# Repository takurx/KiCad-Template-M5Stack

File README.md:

# KiCad-Template-M5Stack
a PCB template of modules of M5Stack with footprints for KiCad.

## for KiCad 9
- Changed file name and folder structure to KiCad 9 from KiCad 6.
    - file name: bf-021.kicad_pcb  <-  bf-021_pcb.kicad
    - folder structure 1: ./bf-021.kicad_pcb  <-  bf-021/bf-021_pcb.kicad
    - folder structure 2: ./meta/  <-  bf-021/meta/

- Example of KiCad 9
```
C:\Users\ChinoKafu\Documents\KiCad\9.0\template\KiCad-Template-M5Stack>tree /f /a .
フォルダー パスの一覧:  ボリューム OS
ボリューム シリアル番号は 2025-1215 です
C:\USERS\CHINOKAFU\DOCUMENTS\KICAD\9.0\TEMPLATE\KICAD-TEMPLATE-M5STACK
|   bf-021.kicad_pcb
|   bf-021.kicad_prl
|   bf-021.kicad_pro
|   bf-021.kicad_sch
|   bf-021_pcb.pdf
|   bf-021_scm.pdf
|   fp-info-cache
|   LICENSE
|   README.md
|
+---meta
|       icon.png
|       info.html
|       meta.json
|       proto.png
|
+---image
|       bf-021.png
|       core2_mbus500.bmp
|       FKGhLbtaQAIh2uu.png
|       M-BUS500.bmp
|
\---pretty
        BF@M5Stack_MBUS.kicad_mod
        BF@MountingHole_2.2mm_M2.kicad_mod
        BF@MountingHole_3.2mm_M3.kicad_mod
```

- Example of KiCad 6
```
C:\Users\ChinoKafu\Documents\KiCad\6.0\template\KiCad-Template-M5Stack>tree /f /a .
フォルダー パスの一覧:  ボリューム OS
ボリューム シリアル番号は 2025-1215 です
C:\USERS\CHINOKAFU\DOCUMENTS\KICAD\6.0\TEMPLATE\KICAD-TEMPLATE-M5STACK
|   bf-021_pcb.pdf
|   bf-021_scm.pdf
|   LICENSE
|   README.md
|
+---bf-021
|   |   bf-021.kicad_pcb
|   |   bf-021.pro
|   |   bf-021.sch
|   |
|   \---meta
|           icon.png
|           info.html
|           proto.png
|
+---image
|       bf-021.png
|       core2_mbus500.bmp
|       FKGhLbtaQAIh2uu.png
|       M-BUS500.bmp
|
\---pretty
        BF@M5Stack_MBUS.kicad_mod
        BF@MountingHole_2.2mm_M2.kicad_mod
        BF@MountingHole_3.2mm_M3.kicad_mod
```

## for KiCad 6
https://github.com/botanicfields/KiCad6-Environment

## for KiCad 5
- Manufacture with a thickness of 1.0 mm.
- M-BUS pin numbers match pin headers and pin sockets in the KiCad library.
- The template has a notch, but it may be actually needed only for the M5Stack controller board.

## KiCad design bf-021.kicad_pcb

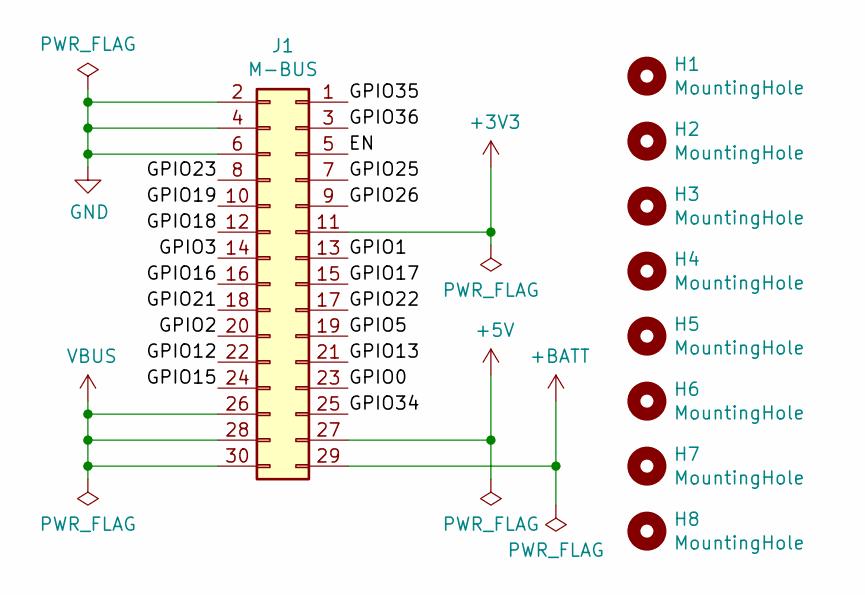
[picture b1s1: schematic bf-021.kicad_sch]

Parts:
H1, H2, H3, H4: MountingHole; BF@MountingHole_3.2mm_M3
H5, H6, H7, H8: MountingHole; BF@MountingHole_2.2mm_M2
J1: M-BUS; BF@M5Stack_MBUS

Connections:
+3V3: J1.11
+5V: J1.27
+BATT: J1.29
/EN: J1.5
/GPIO0: J1.23
/GPIO1: J1.13
/GPIO2: J1.20
/GPIO3: J1.14
/GPIO5: J1.19
/GPIO12: J1.22
/GPIO13: J1.21
/GPIO15: J1.24
/GPIO16: J1.16
/GPIO17: J1.15
/GPIO18: J1.12
/GPIO19: J1.10
/GPIO21: J1.18
/GPIO22: J1.17
/GPIO23: J1.8
/GPIO25: J1.7
/GPIO26: J1.9
/GPIO34: J1.25
/GPIO35: J1.1
/GPIO36: J1.3
GND: J1.2, J1.4, J1.6
VBUS: J1.26, J1.28, J1.30

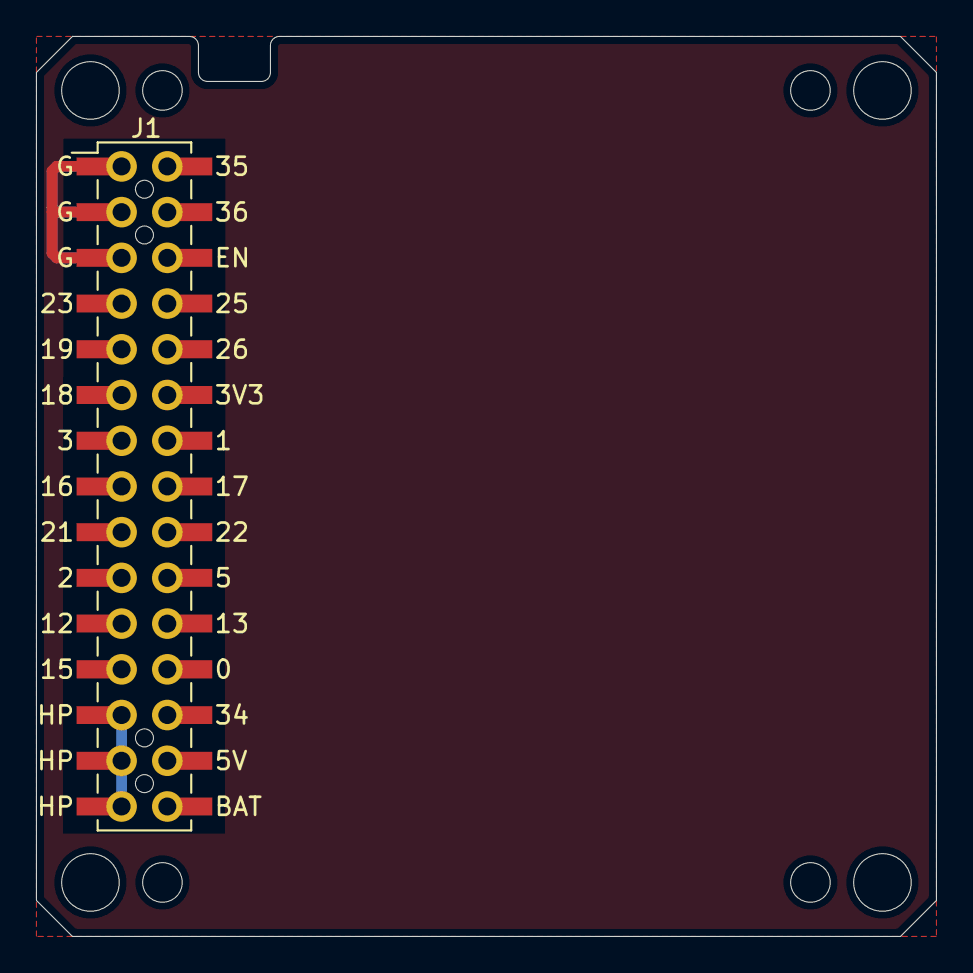
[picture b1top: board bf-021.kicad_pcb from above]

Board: 2 copper layers, 50.0 x 50.0 mm, 9 parts (0 on the bottom side), 2 nets.

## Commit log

2025-12-15 kicad 9.0対応、フォルダ構成変更あり
    kicad 9.0対応、フォルダ構成変更あり
2025-12-15 delete backup
    delete backup
2025-12-15 add gitignore for kicad auto backup file
    add gitignore for kicad auto backup file
2025-12-15 delete non-used file for kicad9
    delete non-used file for kicad9
2025-12-15 update gitignore for lock file when kicad is using
    update gitignore for lock file when kicad is using
2025-12-15 update readme for kicad9
    update readme for kicad9
2025-12-15 change kicad_pcb, setting, unit auto <- inch
    change kicad_pcb, setting, unit auto <- inch

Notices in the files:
bf-021.kicad_pcb:
Copyright 2022 BotanicFields, Inc.
